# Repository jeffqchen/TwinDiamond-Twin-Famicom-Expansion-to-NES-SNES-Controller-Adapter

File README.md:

# Twin Famicom Expansion A to NES/SNES Controller Adapter

This is an adapter for the Nintendo Twin Famicom expansion port A. It is compatible with NES and SNES controllers, plus the NES Zapper lightgun with the 2P NES port.

This adapter also fits well onto the AV Famicom.

## Compatibility Issue

Due to the way different games are coded, [some games](https://github.com/jeffqchen/Famicom-Expansion-Port-Switcher/wiki#significant-titles-affected) can't read the controllers connected on the expansion port (mostly non-Japanese games, designed for the NES).

I have designed an [internal mod](https://github.com/jeffqchen/Famicom-Expansion-Port-Switcher/wiki/Sharp-Twin-Famicom) to deal with this compatibily issue.

-----------

## Parts

- [PCB](https://oshpark.com/shared_projects/1aCic7tG)

- [22x or 28x] Front Pins - Terminal Pins, Male, Machined - [Link](https://github.com/jeffqchen/JeffParts/blob/main/Connectors/Terminal%20Pins/Machined%20Male/info.md)

- [9x] Back Pins - Terminal Pins, Female, Machined - [Link](https://github.com/jeffqchen/JeffParts/blob/main/Connectors/Terminal%20Pins/Machined%20Female/info.md)

- [2x] M2x16mm Hex Screw & Nut - [Link](https://github.com/jeffqchen/JeffParts/blob/main/Parts/M2%20M3%20Hex%20Screw%20%26%20Nut/info.md)

3D Printed Shells

-----------
## Printing

Print everything facing up is a good choice. There really isn't much to it.

The front jacket obviously needs supports.

The plug part might appear split if your line width is set too big. Try 0.35mm and enable "print thin walls" in your slicer. Don't use supports on the the plug. Make sure you don't have too much over-extrusion for the bottom layers as it may clog the holes for the pins. Try an NES plug with the plug part. If they don't go in, clear the NES port holes with a 9/64" drill bit, usually only around the orifice.

The back part doesn't need support either.

-----------
## Assembly

Soldering is not too hard but requires attention. You may want to plug in a controller into the printed plug first, insert the pins in from the back of the printed piece, one port at a time, then fit the PCB over the stumps and solder. Use just enough amount of the solder. Make sure nothing protrudes too much up from the surface.

Repeat the same thing for the back female pins. Fit the 9 pins inside the back piece and then solder them in with small amount of solder.

Note you don't have to populate all the pins, but it makes it look better.

Put the plugs part over the front side through the pins, then seat the assembly into the front jacket piece.

Finally, close it up with the back piece and secure with two sets of M2x16mm screws and nuts.

-----------

## Misc
Thingiverse Page:  
- https://www.thingiverse.com/thing:4882800

-----------

## Special Thanks

Chris Kempson:  
- http://chriskempson.com/posts/nes-controller-to-famicom-adapter/

NesDev Wiki:  
- https://wiki.nesdev.com  

Mike Chi (creator of the very famous RetroTink)  
- https://www.retrotink.com

-----------

Shield: [![CC BY-SA 4.0][cc-by-sa-shield]][cc-by-sa]

This work is licensed under a
[Creative Commons Attribution-ShareAlike 4.0 International License][cc-by-sa].

[![CC BY-SA 4.0][cc-by-sa-image]][cc-by-sa]

[cc-by-sa]: http://creativecommons.org/licenses/by-sa/4.0/
[cc-by-sa-image]: https://licensebuttons.net/l/by-sa/4.0/88x31.png
[cc-by-sa-shield]: https://img.shields.io/badge/License-CC%20BY--SA%204.0-lightgrey.svg

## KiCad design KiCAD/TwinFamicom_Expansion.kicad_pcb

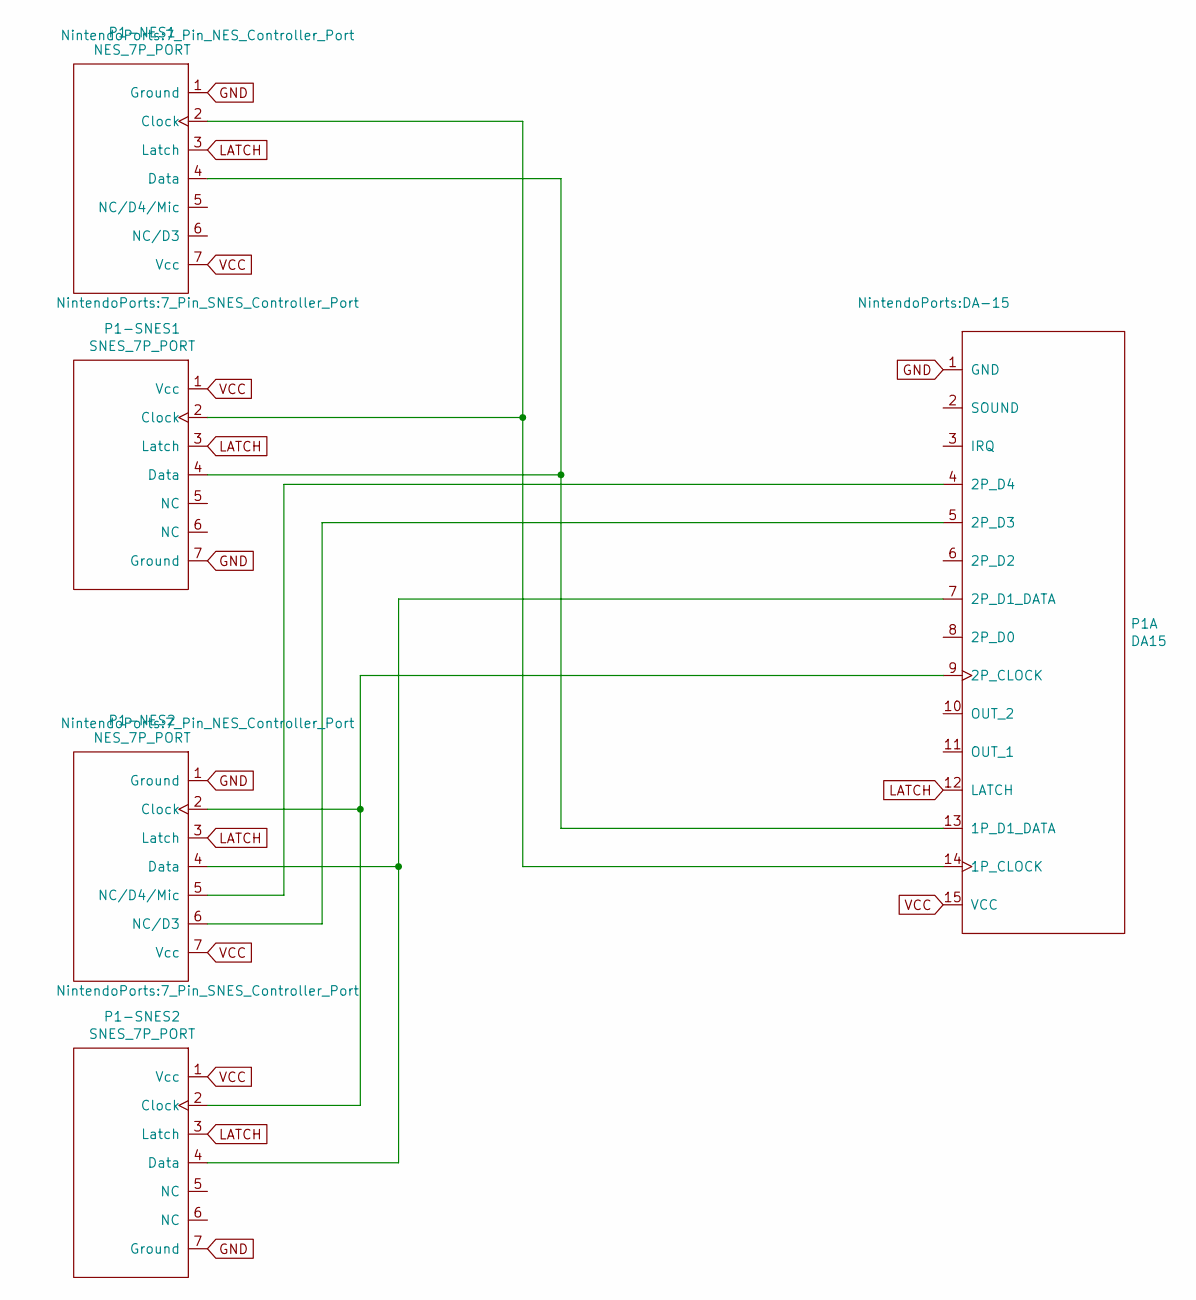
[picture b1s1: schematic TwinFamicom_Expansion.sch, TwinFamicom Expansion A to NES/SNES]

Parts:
P1: DA15; DA-15
P1-NES1, P1-NES2: NES_7P_PORT; 7_Pin_NES_Controller_Port
P1-SNES1, P1-SNES2: SNES_7P_PORT; 7_Pin_SNES_Controller_Port

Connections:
GND: P1.1 (GND), P1-NES1.1 (Ground), P1-NES2.1 (Ground), P1-SNES1.7 (Ground), P1-SNES2.7 (Ground)
LATCH: P1.12 (LATCH), P1-NES1.3 (Latch), P1-NES2.3 (Latch), P1-SNES1.3 (Latch), P1-SNES2.3 (Latch)
unnamed: P1.14 (1P_CLOCK), P1-NES1.2 (Clock), P1-SNES1.2 (Clock)
unnamed: P1.13 (1P_D1_DATA), P1-NES1.4 (Data), P1-SNES1.4 (Data)
unnamed: P1.9 (2P_CLOCK), P1-NES2.2 (Clock), P1-SNES2.2 (Clock)
unnamed: P1.7 (2P_D1_DATA), P1-NES2.4 (Data), P1-SNES2.4 (Data)
unnamed: P1.4 (2P_D4), P1-NES2.5 (NC/D4/Mic)
unnamed: P1.5 (2P_D3), P1-NES2.6 (NC/D3)
VCC: P1.15 (VCC), P1-NES1.7 (Vcc), P1-NES2.7 (Vcc), P1-SNES1.1 (Vcc), P1-SNES2.1 (Vcc)

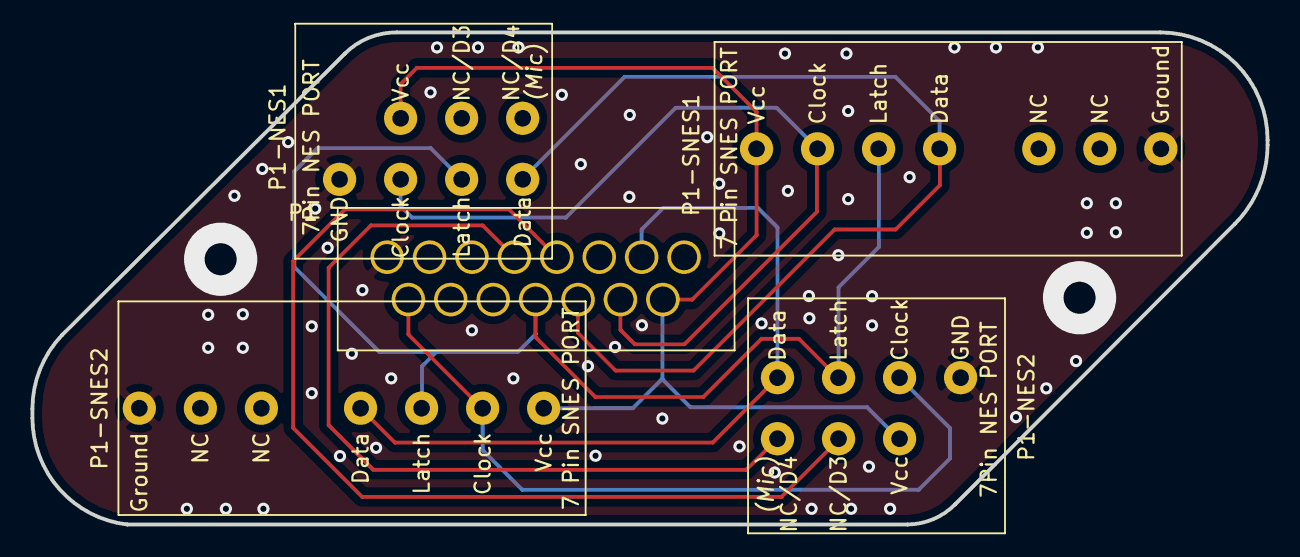
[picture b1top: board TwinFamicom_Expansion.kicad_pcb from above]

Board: 2 copper layers, 81.0 x 32.3 mm, 5 parts (0 on the bottom side), 9 nets.

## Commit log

2021-06-10 Project verified
2021-06-10 Fix readme
2021-10-27 Update fp-info-cache
2021-10-27 Create LICENSE
2022-01-27 Update 3D print
2022-08-09 Change license type
